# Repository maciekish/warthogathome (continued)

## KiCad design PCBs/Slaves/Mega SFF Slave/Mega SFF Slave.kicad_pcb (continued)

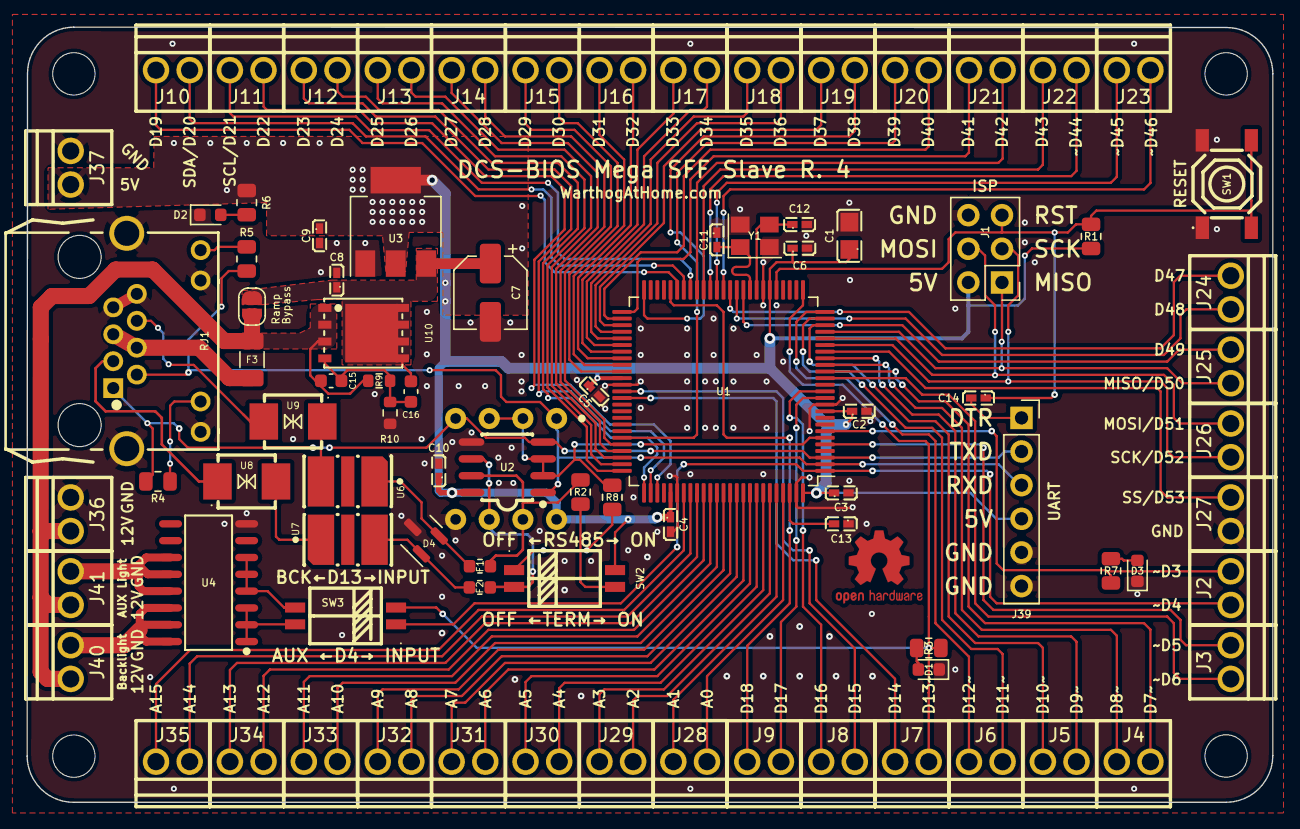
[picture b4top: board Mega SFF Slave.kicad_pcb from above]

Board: 2 copper layers, 94.1 x 58.5 mm, 93 parts (0 on the bottom side), 100 nets.

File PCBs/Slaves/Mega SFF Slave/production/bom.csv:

Designator,Footprint,Quantity,Value,LCSC Part #
U9,DO-214AA_L4.4-W3.6-LS5.3-BI,1,TISP4240M3BJR-S,C840526
J28,CONN-TH_XY308-2.54-2P,1,Screw_Terminal_01x02,C557685
J11,CONN-TH_XY308-2.54-2P,1,Screw_Terminal_01x02,C557685
J2,CONN-TH_XY308-2.54-2P,1,Screw_Terminal_01x02,C557685
J15,CONN-TH_XY308-2.54-2P,1,Screw_Terminal_01x02,C557685
J5,CONN-TH_XY308-2.54-2P,1,Screw_Terminal_01x02,C557685
J36,CONN-TH_XY308-2.54-2P,1,Screw_Terminal_01x02,C557685
J7,CONN-TH_XY308-2.54-2P,1,Screw_Terminal_01x02,C557685
J21,CONN-TH_XY308-2.54-2P,1,Screw_Terminal_01x02,C557685
J17,CONN-TH_XY308-2.54-2P,1,Screw_Terminal_01x02,C557685
J19,CONN-TH_XY308-2.54-2P,1,Screw_Terminal_01x02,C557685
J4,CONN-TH_XY308-2.54-2P,1,Screw_Terminal_01x02,C557685
J9,CONN-TH_XY308-2.54-2P,1,Screw_Terminal_01x02,C557685
J6,CONN-TH_XY308-2.54-2P,1,Screw_Terminal_01x02,C557685
J20,CONN-TH_XY308-2.54-2P,1,Screw_Terminal_01x02,C557685
J10,CONN-TH_XY308-2.54-2P,1,Screw_Terminal_01x02,C557685
J40,CONN-TH_XY308-2.54-2P,1,Screw_Terminal_01x02,C557685
J30,CONN-TH_XY308-2.54-2P,1,Screw_Terminal_01x02,C557685
J37,CONN-TH_XY308-2.54-2P,1,Screw_Terminal_01x02,C557685
J33,CONN-TH_XY308-2.54-2P,1,Screw_Terminal_01x02,C557685
J8,CONN-TH_XY308-2.54-2P,1,Screw_Terminal_01x02,C557685
J25,CONN-TH_XY308-2.54-2P,1,Screw_Terminal_01x02,C557685
J12,CONN-TH_XY308-2.54-2P,1,Screw_Terminal_01x02,C557685
J3,CONN-TH_XY308-2.54-2P,1,Screw_Terminal_01x02,C557685
J14,CONN-TH_XY308-2.54-2P,1,Screw_Terminal_01x02,C557685
J32,CONN-TH_XY308-2.54-2P,1,Screw_Terminal_01x02,C557685
J18,CONN-TH_XY308-2.54-2P,1,Screw_Terminal_01x02,C557685
J23,CONN-TH_XY308-2.54-2P,1,Screw_Terminal_01x02,C557685
J31,CONN-TH_XY308-2.54-2P,1,Screw_Terminal_01x02,C557685
J27,CONN-TH_XY308-2.54-2P,1,Screw_Terminal_01x02,C557685
J13,CONN-TH_XY308-2.54-2P,1,Screw_Terminal_01x02,C557685
J16,CONN-TH_XY308-2.54-2P,1,Screw_Terminal_01x02,C557685
J22,CONN-TH_XY308-2.54-2P,1,Screw_Terminal_01x02,C557685
J24,CONN-TH_XY308-2.54-2P,1,Screw_Terminal_01x02,C557685
J29,CONN-TH_XY308-2.54-2P,1,Screw_Terminal_01x02,C557685
J26,CONN-TH_XY308-2.54-2P,1,Screw_Terminal_01x02,C557685
J41,CONN-TH_XY308-2.54-2P,1,Screw_Terminal_01x02,C557685
J35,CONN-TH_XY308-2.54-2P,1,Screw_Terminal_01x02,C557685
J34,CONN-TH_XY308-2.54-2P,1,Screw_Terminal_01x02,C557685
C4,C0402,1,1uF,C52923
SW1,SW-SMD_4P-L5.1-W5.1-P3.70-LS6.5-TL-2,1,SW_MEC_5E,C318884
U5,DIP-8_W7.62mm,1,MAX487ESA+T,C9953
J1,PinHeader_2x03_P2.54mm_Vertical,1,AVR-ISP-6,C492420
D4,SOT-23,1,SM712_SOT23,C558433
U4,SOP-16_L10.0-W3.9-P1.27-LS6.0-BL,1,ULN2003A,C7512
R1,R_0805_2012Metric,1,10K,C17414
C6,C0402,1,1uF,C52923
C8,C0402,1,10uF,C15525
SW3,SW-SMD_DSHP02TSGER,1,SW_DIP_x02,C367376
RJ1,RJ45-TH_B-1-1,1,RJ45-B-1*1,C138392
J39,PinSocket_1x06_P2.54mm_Vertical,1,Conn_01x06_Female,C40877
U6,DIO-SMD_3P-L6.5-W4.0-BI,1,TBU-CA065-200-WH,C913221
U7,DIO-SMD_3P-L6.5-W4.0-BI,1,TBU-CA065-200-WH,C913221
C9,C0402,1,1uF,C52923
C12,C0402,1,15pF,C1548
F1,Fuse_0603_1608Metric,1,100mA,C207238
C7,CP_Elec_5x5.4,1,47uF,C96178
R7,R_0805_2012Metric,1,1K,C17513
SW2,SW-SMD_DSHP02TSGER,1,SW_DIP_x02,C367376
C13,C0402,1,100nF,C1525
U2,SOIC-8_L5.0-W4.0-P1.27-LS6.0-BL,1,MAX487ESA+T,C9953
R2,R_0805_2012Metric,1,120R,C17437
U3,SOT-223-3_TabPin2,1,AMS1117-5.0,C6187
C2,C0402,1,1uF,C52923
C14,C0402,1,100nF,C1525
U10,DFN-8_L5.9-W5.2-P1.27-LS6.2-BL,1,HY15P03C2,C123687
D2,LED_0603_1608Metric,1,LED,C72041
C16,C_0603_1608Metric,1,47nF,C1622
U1,TQFP-100_14x14mm_P0.5mm,1,ATmega2560-16A,C22460
C1,C0805,1,4.7uF,C1779
R3,R_0805_2012Metric,1,1K,C17513
C5,C0402,1,1uF,C52923
R4,R_0805_2012Metric,1,1.8K,C17398
U8,DO-214AA_L4.4-W3.6-LS5.3-BI,1,TISP4240M3BJR-S,C840526
D1,LED_0603_1608Metric,1,LED,C72041
R9,R_0603_1608Metric,1,10M,C7250
R8,R_0805_2012Metric,1,1K,C17513
C3,C0402,1,1uF,C52923
C10,C0402,1,1uF,C52923
C15,C_0603_1608Metric,1,470nF,C1623
JP1,SolderJumper-2_P1.3mm_Open_RoundedPad1.0x1.5mm,1,Solder,
F3,Fuse_1206_3216Metric,1,500mA,C369159
C11,C0402,1,15pF,C1548
R10,R_0603_1608Metric,1,1M,C22935
Y1,Crystal_SMD_3225-4Pin_3.2x2.5mm,1,Crystal_GND24,C13738
F2,Fuse_0603_1608Metric,1,100mA,C207238
R5,R_0805_2012Metric,1,1.8K,C17398
R6,R_0805_2012Metric,1,1K,C17513
D3,LED_0603_1608Metric,1,LED,C72041

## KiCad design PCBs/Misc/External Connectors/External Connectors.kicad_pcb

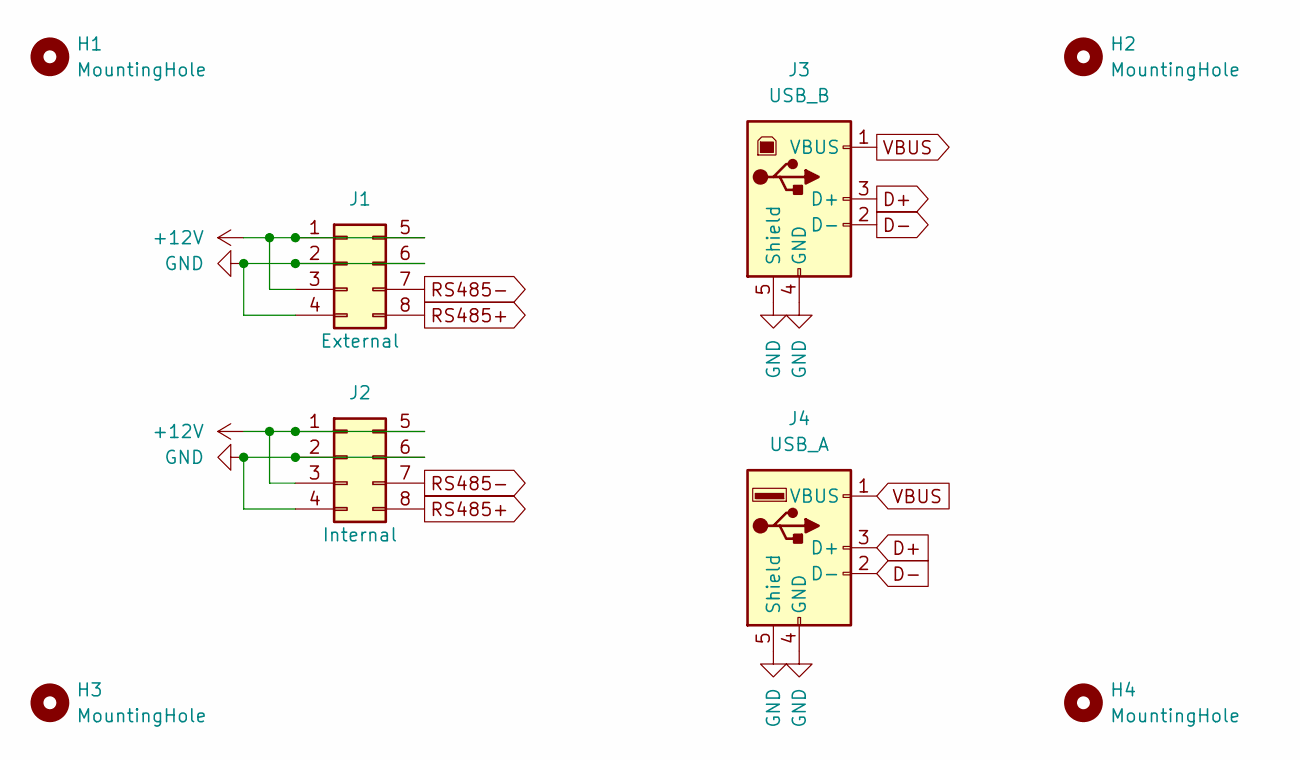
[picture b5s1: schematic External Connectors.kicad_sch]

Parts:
H1, H2, H3, H4: MountingHole; MountingHole_3.2mm_M3
J1, J2: Conn_02x04_Top_Bottom; Molex Micro-Fit 3.0 43045-0800; LCSC C234189
J3: USB_B; USB-B-TH_67068-8000; LCSC C114097
J4: USB_A; USB-A-TH_USB-302-T; LCSC C86461

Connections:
+12V: J1.1, J1.3, J1.5, J2.1, J2.3, J2.5
D+: J3.3 (D+), J4.3 (D+)
D-: J3.2 (D-), J4.2 (D-)
GND: J1.2, J1.4, J1.6, J2.2, J2.4, J2.6, J3.4 (GND), J3.5 (Shield), J4.4 (GND), J4.5 (Shield)
RS485+: J1.8, J2.8
RS485-: J1.7, J2.7
VBUS: J3.1 (VBUS), J4.1 (VBUS)

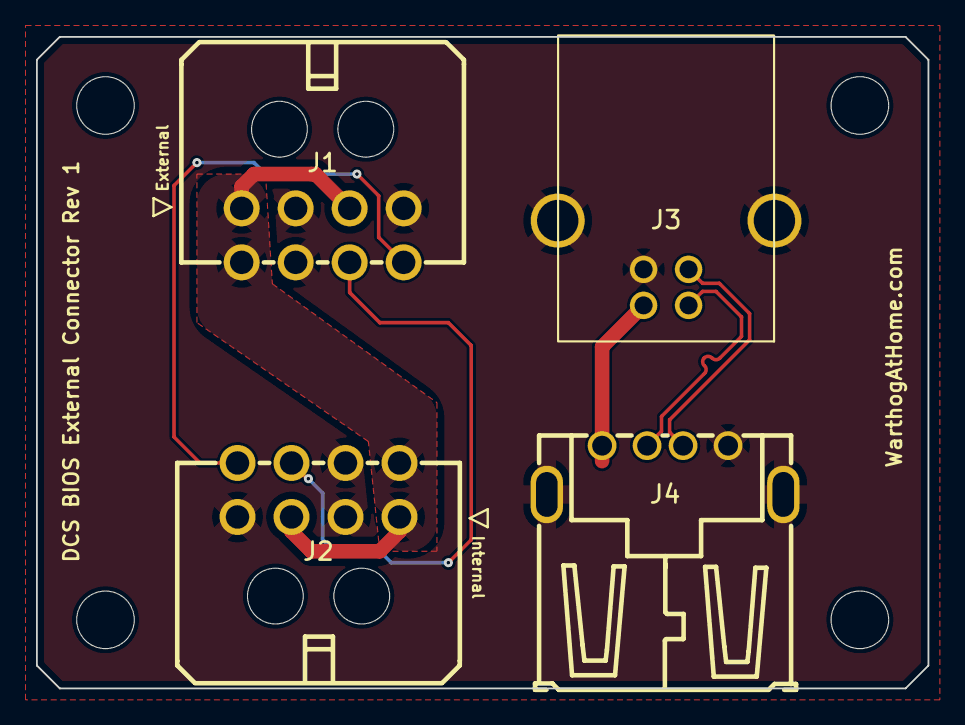
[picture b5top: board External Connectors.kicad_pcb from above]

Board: 2 copper layers, 49.5 x 36.2 mm, 8 parts (0 on the bottom side), 7 nets.

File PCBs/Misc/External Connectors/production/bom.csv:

Designator,Footprint,Quantity,Value,LCSC Part #
J4,USB-A-TH_USB-302-T,1,USB_A,C86461
J3,USB-B-TH_67068-8000,1,USB_B,C114097
J1,Molex Micro-Fit 3.0 43045-0800,1,Conn_02x04_Top_Bottom,C234189
J2,Molex Micro-Fit 3.0 43045-0800,1,Conn_02x04_Top_Bottom,C234189

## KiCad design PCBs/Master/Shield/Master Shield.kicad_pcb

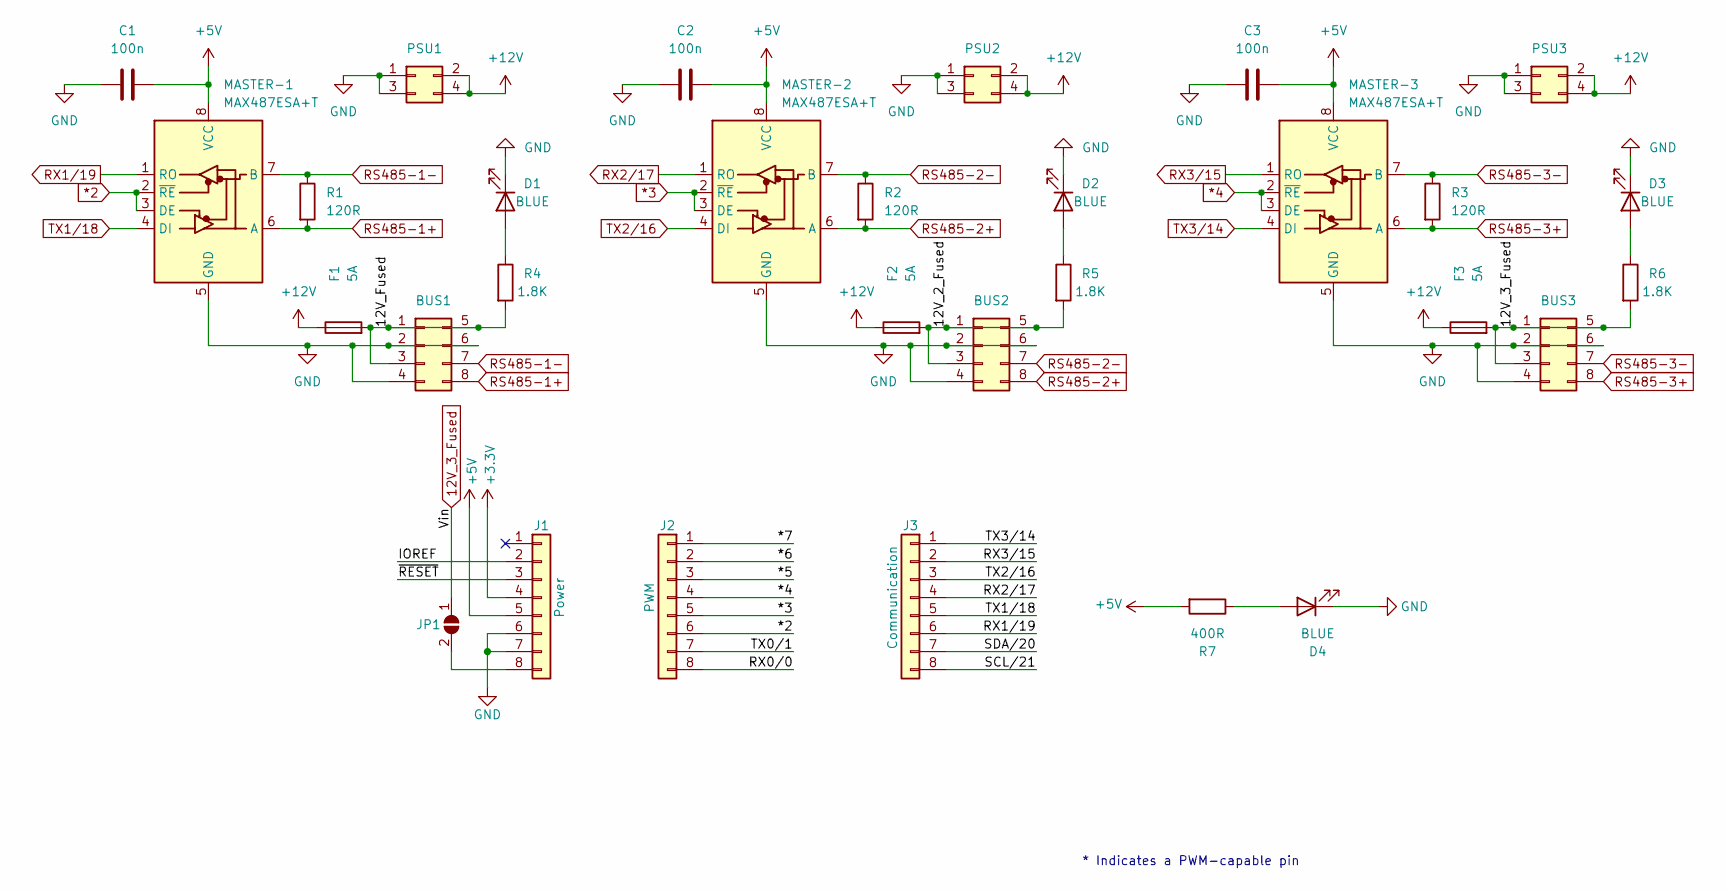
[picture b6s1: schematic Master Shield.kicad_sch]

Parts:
BUS1, BUS2, BUS3: Conn_02x04_Top_Bottom; CONN-TH_430450812; LCSC C277661
C1, C2, C3: 100n; C0402; LCSC C1525
D1, D2, D3, D4: BLUE; LED_0603_1608Metric; LCSC C72041
F1, F2, F3: 5A; FUSE_BK-6013; LCSC C492610
J1: Power; PinHeader_1x08_P2.54mm_Vertical; LCSC C124381
J2: PWM; PinHeader_1x08_P2.54mm_Vertical; LCSC C124381
J3: Communication; PinHeader_1x08_P2.54mm_Vertical; LCSC C124381
JP1: SolderJumper_2_Open; SolderJumper-2_P1.3mm_Open_RoundedPad1.0x1.5mm
MASTER-1, MASTER-2, MASTER-3: MAX487ESA+T; SOIC-8_L5.0-W4.0-P1.27-LS6.0-BL; LCSC C9953
PSU1, PSU2, PSU3: Conn_02x02_Top_Bottom; CONN-TH_0430450400
R1, R2, R3: 120R; R_0805_2012Metric; LCSC C17437
R4, R5, R6: 1.8K; R_0805_2012Metric; LCSC C17398
R7: 400R; R_0805_2012Metric; LCSC C17655

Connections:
12V_3_Fused: BUS3.1, BUS3.3, BUS3.5, F3.2, JP1.1 (A), R6.2
*2: J2.6, MASTER-1.2 (~RE), MASTER-1.3 (DE)
*3: J2.5, MASTER-2.2 (~RE), MASTER-2.3 (DE)
*4: J2.4, MASTER-3.2 (~RE), MASTER-3.3 (DE)
+3V3: J1.4
+5V: C1.2, C2.2, C3.2, J1.5, MASTER-1.8 (VCC), MASTER-2.8 (VCC), MASTER-3.8 (VCC), R7.2
/12V_2_Fused: BUS2.1, BUS2.3, BUS2.5, F2.2, R5.2
/12V_Fused: BUS1.1, BUS1.3, BUS1.5, F1.2, R4.2
/*5: J2.3
/*6: J2.2
/*7: J2.1
/IOREF: J1.2
/RX0/0: J2.8
/SCL/21: J3.8
/SDA/20: J3.7
/TX0/1: J2.7
/~RESET: J1.3
GND: BUS1.2, BUS1.4, BUS1.6, BUS2.2, BUS2.4, BUS2.6, BUS3.2, BUS3.4, BUS3.6, C1.1, C2.1, C3.1, D1.1 (K), D2.1 (K), D3.1 (K), D4.1 (K), J1.6, J1.7, MASTER-1.5 (GND), MASTER-2.5 (GND), MASTER-3.5 (GND), PSU1.1, PSU1.3, PSU2.1, PSU2.3, PSU3.1, PSU3.3
unnamed: D1.2 (A), R4.1
unnamed: D2.2 (A), R5.1
unnamed: D3.2 (A), R6.1
unnamed: D4.2 (A), R7.1
unnamed: J1.8, JP1.2 (B)
RS485-1+: BUS1.8, MASTER-1.6 (A), R1.2
RS485-1-: BUS1.7, MASTER-1.7 (B), R1.1
RS485-2+: BUS2.8, MASTER-2.6 (A), R2.2
RS485-2-: BUS2.7, MASTER-2.7 (B), R2.1
RS485-3+: BUS3.8, MASTER-3.6 (A), R3.2
RS485-3-: BUS3.7, MASTER-3.7 (B), R3.1
RX1/19: J3.6, MASTER-1.1 (RO)
RX2/17: J3.4, MASTER-2.1 (RO)
RX3/15: J3.2, MASTER-3.1 (RO)
TX1/18: J3.5, MASTER-1.4 (DI)
TX2/16: J3.3, MASTER-2.4 (DI)
TX3/14: J3.1, MASTER-3.4 (DI)

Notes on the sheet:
* Indicates a PWM-capable pin

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
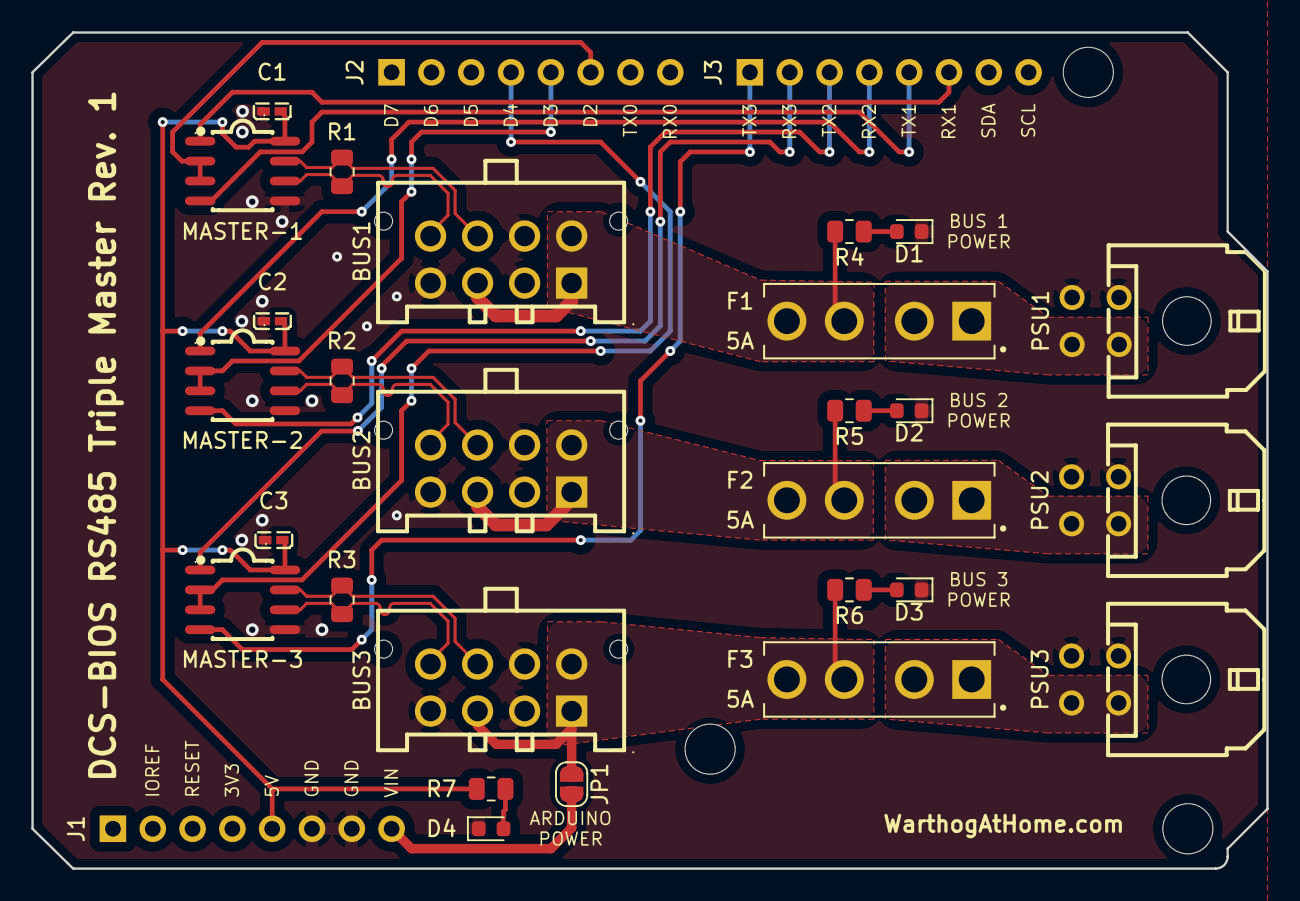
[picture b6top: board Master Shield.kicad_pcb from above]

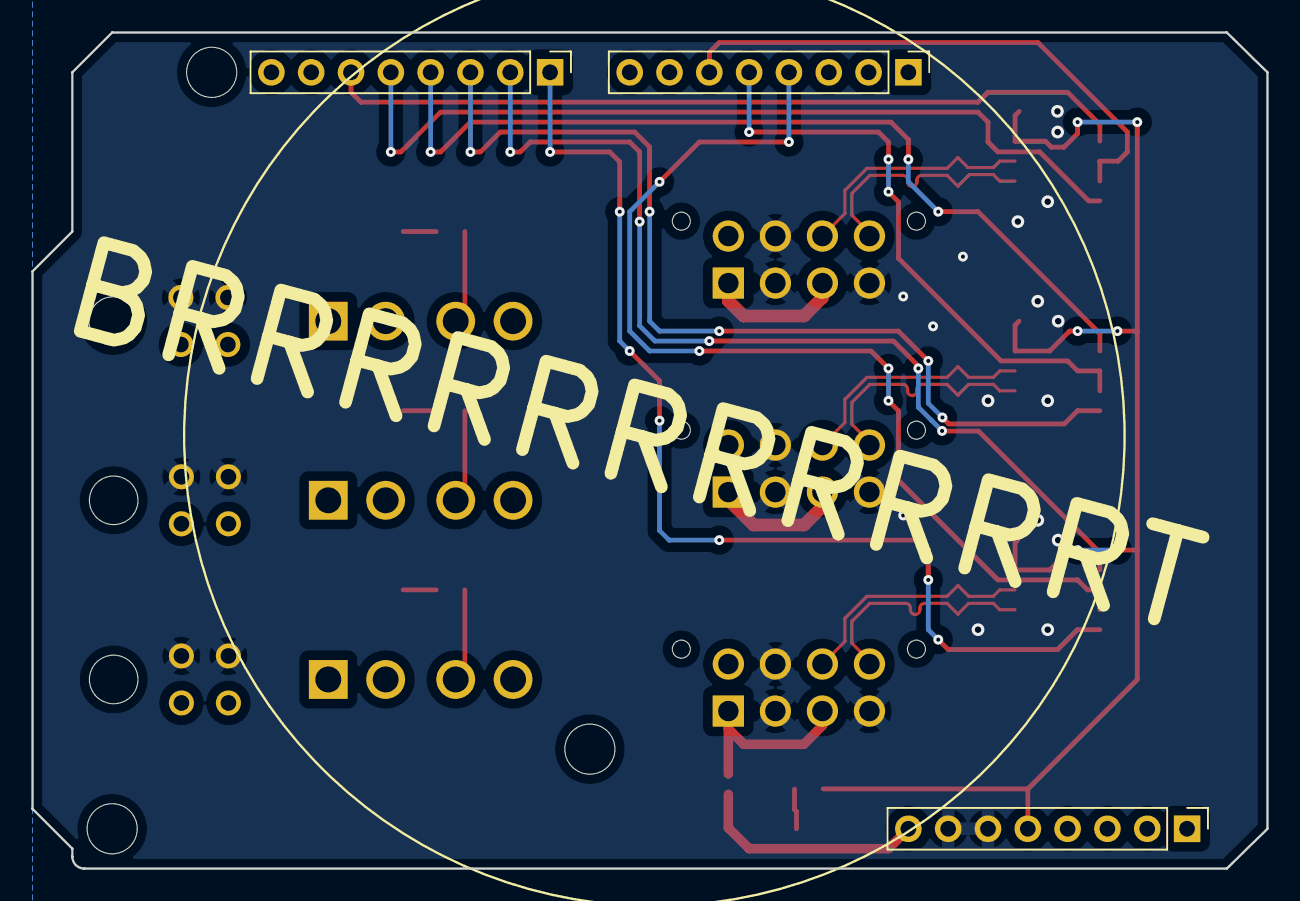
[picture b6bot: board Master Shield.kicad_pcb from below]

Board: 2 copper layers, 78.8 x 53.3 mm, 33 parts (3 on the bottom side), 28 nets.

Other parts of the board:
MH4, MH5, MH6: MountingHole_3.2mm

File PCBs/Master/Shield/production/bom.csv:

Designator,Footprint,Quantity,Value,LCSC Part #
R2,R_0805_2012Metric,1,120R,C17437
MASTER-2,SOIC-8_L5.0-W4.0-P1.27-LS6.0-BL,1,MAX487ESA+T,C9953
R4,R_0805_2012Metric,1,1.8K,C17398
D3,LED_0603_1608Metric,1,BLUE,C72041
BUS3,CONN-TH_430450812,1,Conn_02x04_Top_Bottom,C277661
C1,C0402,1,100n,C1525
C3,C0402,1,100n,C1525
R5,R_0805_2012Metric,1,1.8K,C17398
MASTER-1,SOIC-8_L5.0-W4.0-P1.27-LS6.0-BL,1,MAX487ESA+T,C9953
D1,LED_0603_1608Metric,1,BLUE,C72041
D2,LED_0603_1608Metric,1,BLUE,C72041
JP1,SolderJumper-2_P1.3mm_Open_RoundedPad1.0x1.5mm,1,SolderJumper_2_Open,
D4,LED_0603_1608Metric,1,BLUE,C72041
C2,C0402,1,100n,C1525
R6,R_0805_2012Metric,1,1.8K,C17398
R7,R_0805_2012Metric,1,400R,C17655
BUS2,CONN-TH_430450812,1,Conn_02x04_Top_Bottom,C277661
MASTER-3,SOIC-8_L5.0-W4.0-P1.27-LS6.0-BL,1,MAX487ESA+T,C9953
R1,R_0805_2012Metric,1,120R,C17437
R3,R_0805_2012Metric,1,120R,C17437
BUS1,CONN-TH_430450812,1,Conn_02x04_Top_Bottom,C277661
J1,PinHeader_1x08_P2.54mm_Vertical,1,Power,C124381
J2,PinHeader_1x08_P2.54mm_Vertical,1,PWM,C124381
J3,PinHeader_1x08_P2.54mm_Vertical,1,Communication,C124381

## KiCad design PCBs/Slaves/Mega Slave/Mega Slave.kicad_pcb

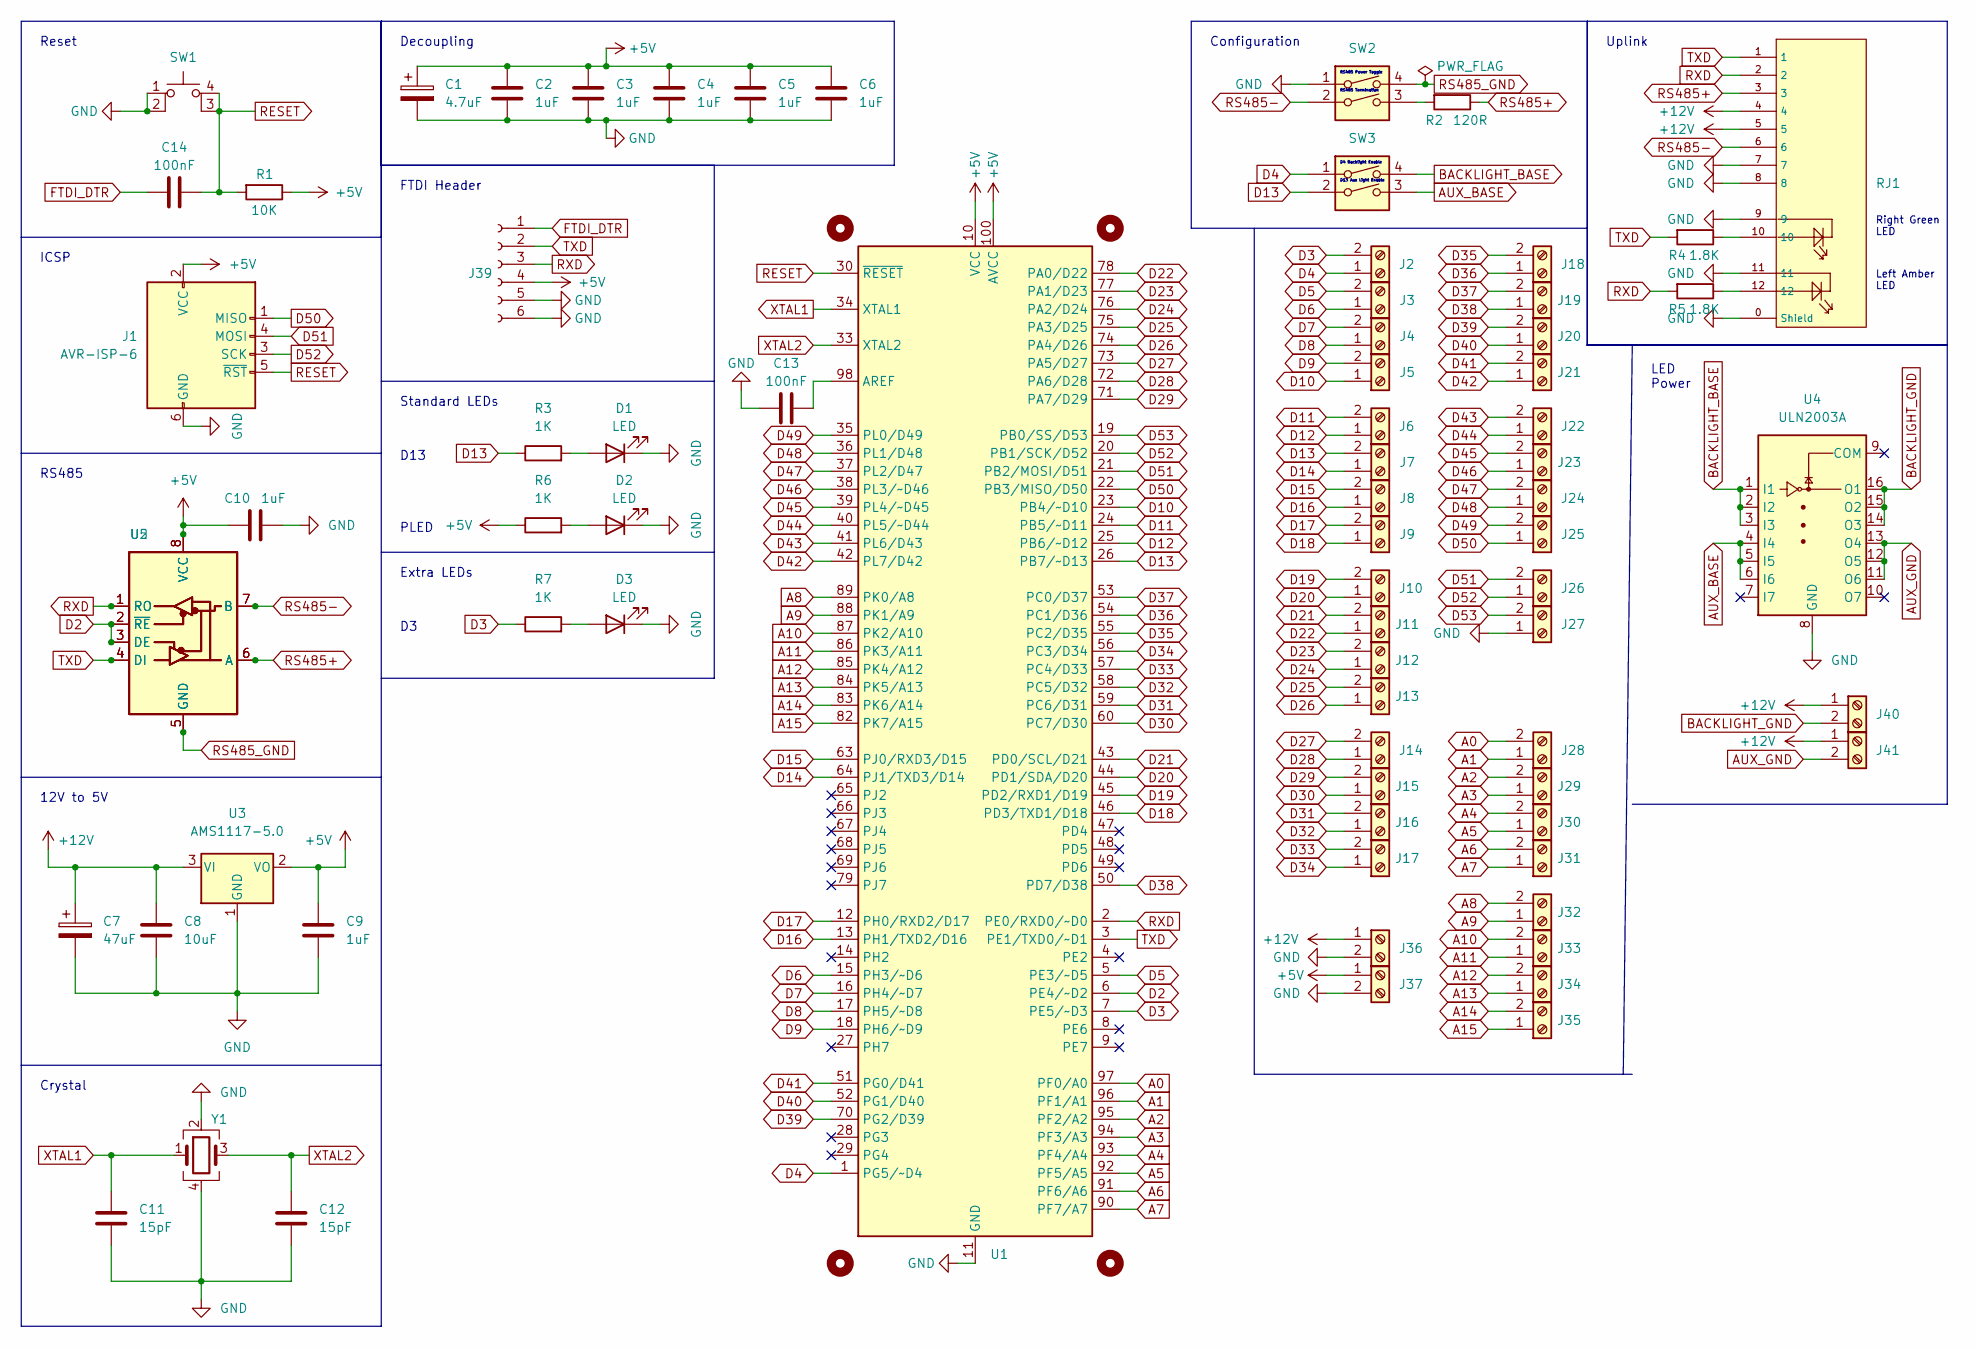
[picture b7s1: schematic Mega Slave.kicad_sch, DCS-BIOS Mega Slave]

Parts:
C1: 4.7uF; C0805; LCSC C1779
C2, C3, C4, C5, C6, C9, C10: 1uF; C0402; LCSC C52923
C7: 47uF; CP_Elec_5x5.4; LCSC C96178
C8: 10uF; C0402; LCSC C15525
C11, C12: 15pF; C0402; LCSC C1548
C13, C14: 100nF; C0402; LCSC C1525
D1, D2, D3: LED; LED_0603_1608Metric; LCSC C72041
H1, H2, H3, H4: MountingHole; MountingHole_3.2mm_M3
J1: AVR-ISP-6; PinHeader_2x03_P2.54mm_Vertical; LCSC C492420
J2, J3, J4, J5, J6, J7, J8, J9, J10, J11, J12, J13, J14, J15, J16, J17, J18, J19, J20, J21, J22, J23, J24, J25, J26, J27, J28, J29, J30, J31, J32, J33, J34, J35, J36, J37, J40, J41: Screw_Terminal_01x02; CONN-TH_WJ126V-5.0-2P; LCSC C8404
J39: Conn_01x06_Female; PinSocket_1x06_P2.54mm_Vertical; LCSC C40877
R1: 10K; R_0805_2012Metric; LCSC C17414
R2: 120R; R_0805_2012Metric; LCSC C17437
R3, R6, R7: 1K; R_0805_2012Metric; LCSC C17513
R4, R5: 1.8K; R_0805_2012Metric; LCSC C17398
RJ1: RJ45-B-1*1; RJ45-TH_B-1-1; LCSC C138392
SW1: SW_MEC_5E; SW-SMD_4P-L5.1-W5.1-P3.70-LS6.5-TL-2; LCSC C318884
SW2, SW3: SW_DIP_x02; SW-SMD_DSHP02TSGER; LCSC C367376
U1: ATmega2560-16A; TQFP-100_14x14mm_P0.5mm; LCSC C22460
U2: MAX487ESA+T; SOIC-8_L5.0-W4.0-P1.27-LS6.0-BL; LCSC C9953
U3: AMS1117-5.0; SOT-223-3_TabPin2; LCSC C6187
U4: ULN2003A; SOP-16_L10.0-W3.9-P1.27-LS6.0-BL; LCSC C7512
U5: MAX487ESA+T; DIP-8_W7.62mm; LCSC C9953
Y1: Crystal_GND24; Crystal_SMD_3225-4Pin_3.2x2.5mm; LCSC C13738

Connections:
+5V: C1.1, C2.1, C3.1, C4.1, C5.1, C6.1, C9.1, C10.1, J1.2 (VCC), J37.1, J39.4, R1.1, R6.1, U1.10 (VCC), U1.31 (VCC), U1.61 (VCC), U1.80 (VCC), U1.100 (AVCC), U2.8 (VCC), U3.2 (VO), U5.8 (VCC)
+12V: C7.1, C8.1, J36.1, J40.1, J41.1, RJ1.4, RJ1.5, U3.3 (VI)
A0: J28.2, U1.97 (PF0/A0)
A1: J28.1, U1.96 (PF1/A1)
A2: J29.2, U1.95 (PF2/A2)
A3: J29.1, U1.94 (PF3/A3)
A4: J30.2, U1.93 (PF4/A4)
A5: J30.1, U1.92 (PF5/A5)
A6: J31.2, U1.91 (PF6/A6)
A7: J31.1, U1.90 (PF7/A7)
A8: J32.2, U1.89 (PK0/A8)
A9: J32.1, U1.88 (PK1/A9)
A10: J33.2, U1.87 (PK2/A10)
A11: J33.1, U1.86 (PK3/A11)
A12: J34.2, U1.85 (PK4/A12)
A13: J34.1, U1.84 (PK5/A13)
A14: J35.2, U1.83 (PK6/A14)
A15: J35.1, U1.82 (PK7/A15)
AUX_BASE: SW3.3, U4.4 (I4), U4.5 (I5), U4.6 (I6)
AUX_GND: J41.2, U4.11 (O6), U4.12 (O5), U4.13 (O4)
BACKLIGHT_BASE: SW3.4, U4.1 (I1), U4.2 (I2), U4.3 (I3)
BACKLIGHT_GND: J40.2, U4.14 (O3), U4.15 (O2), U4.16 (O1)
D2: U1.6 (PE4/~D2), U2.2 (~RE), U2.3 (DE), U5.2 (~RE), U5.3 (DE)
D3: J2.2, R7.1, U1.7 (PE5/~D3)
D4: J2.1, SW3.1, U1.1 (PG5/~D4)
D5: J3.2, U1.5 (PE3/~D5)
D6: J3.1, U1.15 (PH3/~D6)
D7: J4.2, U1.16 (PH4/~D7)
D8: J4.1, U1.17 (PH5/~D8)
D9: J5.2, U1.18 (PH6/~D9)
D10: J5.1, U1.23 (PB4/~D10)
D11: J6.2, U1.24 (PB5/~D11)
D12: J6.1, U1.25 (PB6/~D12)
D13: J7.2, R3.1, SW3.2, U1.26 (PB7/~D13)
D14: J7.1, U1.64 (PJ1/TXD3/D14)
D15: J8.2, U1.63 (PJ0/RXD3/D15)
D16: J8.1, U1.13 (PH1/TXD2/D16)
D17: J9.2, U1.12 (PH0/RXD2/D17)
D18: J9.1, U1.46 (PD3/TXD1/D18)
D19: J10.2, U1.45 (PD2/RXD1/D19)
D20: J10.1, U1.44 (PD1/SDA/D20)
D21: J11.2, U1.43 (PD0/SCL/D21)
D22: J11.1, U1.78 (PA0/D22)
D23: J12.2, U1.77 (PA1/D23)
D24: J12.1, U1.76 (PA2/D24)
D25: J13.2, U1.75 (PA3/D25)
D26: J13.1, U1.74 (PA4/D26)
D27: J14.2, U1.73 (PA5/D27)
D28: J14.1, U1.72 (PA6/D28)
D29: J15.2, U1.71 (PA7/D29)
D30: J15.1, U1.60 (PC7/D30)
D31: J16.2, U1.59 (PC6/D31)
D32: J16.1, U1.58 (PC5/D32)
D33: J17.2, U1.57 (PC4/D33)
D34: J17.1, U1.56 (PC3/D34)
D35: J18.2, U1.55 (PC2/D35)
D36: J18.1, U1.54 (PC1/D36)
D37: J19.2, U1.53 (PC0/D37)
D38: J19.1, U1.50 (PD7/D38)
D39: J20.2, U1.70 (PG2/D39)
D40: J20.1, U1.52 (PG1/D40)
D41: J21.2, U1.51 (PG0/D41)
D42: J21.1, U1.42 (PL7/D42)
D43: J22.2, U1.41 (PL6/D43)
D44: J22.1, U1.40 (PL5/~D44)
D45: J23.2, U1.39 (PL4/~D45)
D46: J23.1, U1.38 (PL3/~D46)
D47: J24.2, U1.37 (PL2/D47)
D48: J24.1, U1.36 (PL1/D48)
D49: J25.2, U1.35 (PL0/D49)
D50: J1.1 (MISO), J25.1, U1.22 (PB3/MISO/D50)
D51: J1.4 (MOSI), J26.2, U1.21 (PB2/MOSI/D51)
D52: J1.3 (SCK), J26.1, U1.20 (PB1/SCK/D52)
D53: J27.2, U1.19 (PB0/SS/D53)
FTDI_DTR: C14.2, J39.1
GND: C1.2, C2.2, C3.2, C4.2, C5.2, C6.2, C7.2, C8.2, C9.2, C10.2, C11.1, C12.2, C13.1, D1.1 (K), D2.1 (K), D3.1 (K), J1.6 (GND), J27.1, J36.2, J37.2, J39.5, J39.6, RJ1.0 (Shield), RJ1.7, RJ1.8, RJ1.9, RJ1.11, SW1.1, SW1.2, SW2.1, U1.11 (GND), U1.32 (GND), U1.62 (GND), U1.81 (GND), U1.99 (GND), U3.1 (GND), U4.8 (GND), Y1.2, Y1.4
unnamed: C13.2, U1.98 (AREF)
unnamed: D1.2 (A), R3.2
unnamed: D2.2 (A), R6.2
unnamed: D3.2 (A), R7.2
unnamed: R2.2, SW2.3
unnamed: R4.1, RJ1.10
unnamed: R5.1, RJ1.12
RESET: C14.1, J1.5 (~RST), R1.2, SW1.3 (K), SW1.4 (A), U1.30 (~RESET)
RS485+: R2.1, RJ1.3, U2.6 (A), U5.6 (A)
RS485-: RJ1.6, SW2.2, U2.7 (B), U5.7 (B)
RS485_GND: SW2.4, U2.5 (GND), U5.5 (GND)
RXD: J39.3, R5.2, RJ1.2, U1.2 (PE0/RXD0/~D0), U2.1 (RO), U5.1 (RO)
TXD: J39.2, R4.2, RJ1.1, U1.3 (PE1/TXD0/~D1), U2.4 (DI), U5.4 (DI)
XTAL1: C11.2, U1.34 (XTAL1), Y1.1
XTAL2: C12.1, U1.33 (XTAL2), Y1.3

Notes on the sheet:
RS485
Reset
LED Power
Right Green LED
Configuration
Crystal
Standard LEDs
Decoupling
Left Amber LED
RS485 Termination
Extra LEDs
D4 Backlight Enable
12V to 5V
RS485 Power Toggle
Uplink
D13 Aux Light Enable
D13
FTDI Header
ICSP
PLED

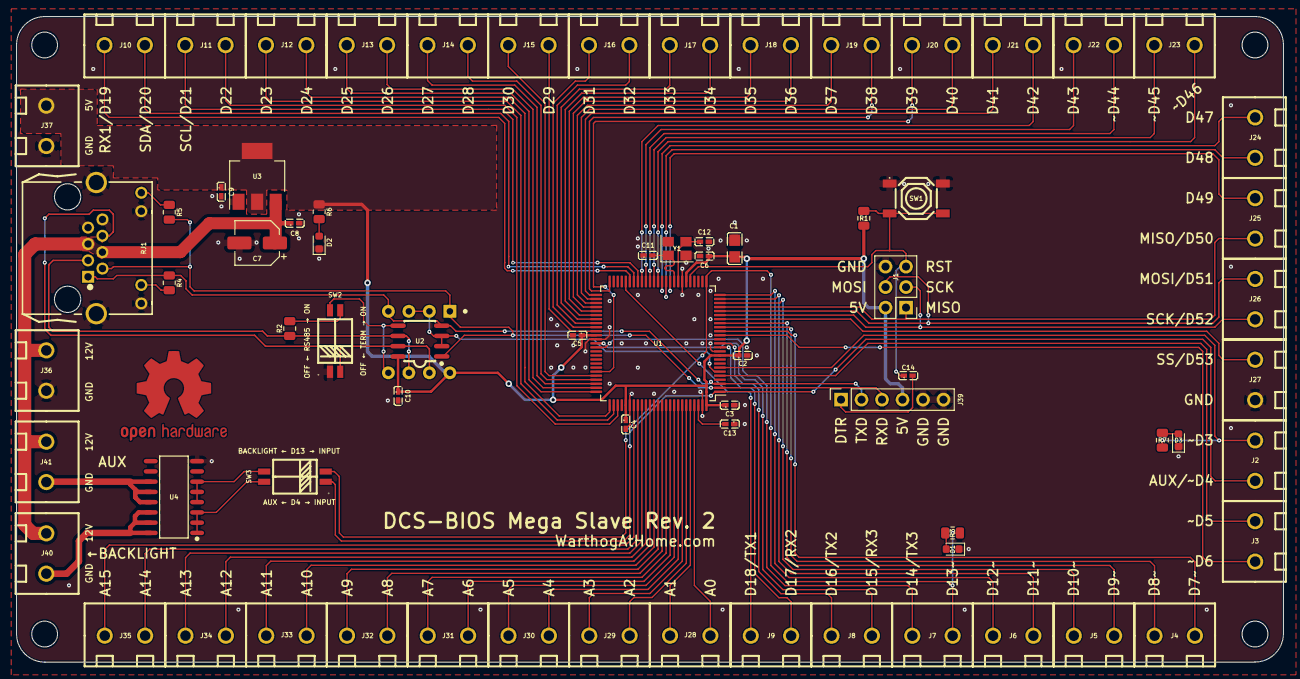
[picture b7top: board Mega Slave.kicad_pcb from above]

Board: 2 copper layers, 157.0 x 80.0 mm, 78 parts (0 on the bottom side), 91 nets.

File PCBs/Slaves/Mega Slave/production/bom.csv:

Designator,Footprint,Quantity,Value,LCSC Part #
J28,CONN-TH_WJ126V-5.0-2P,1,Screw_Terminal_01x02,C557685
J11,CONN-TH_WJ126V-5.0-2P,1,Screw_Terminal_01x02,C557685
C4,C0402,1,1uF,C52923
J2,CONN-TH_WJ126V-5.0-2P,1,Screw_Terminal_01x02,C557685
J15,CONN-TH_WJ126V-5.0-2P,1,Screw_Terminal_01x02,C557685
SW1,SW-SMD_4P-L5.1-W5.1-P3.70-LS6.5-TL-2,1,SW_MEC_5E,C318884
U5,DIP-8_W7.62mm,1,MAX487ESA+T,C9953
J1,PinHeader_2x03_P2.54mm_Vertical,1,AVR-ISP-6,C492420
J5,CONN-TH_WJ126V-5.0-2P,1,Screw_Terminal_01x02,C557685
J36,CONN-TH_WJ126V-5.0-2P,1,Screw_Terminal_01x02,C557685
U4,SOP-16_L10.0-W3.9-P1.27-LS6.0-BL,1,ULN2003A,C7512
J7,CONN-TH_WJ126V-5.0-2P,1,Screw_Terminal_01x02,C557685
J21,CONN-TH_WJ126V-5.0-2P,1,Screw_Terminal_01x02,C557685
J17,CONN-TH_WJ126V-5.0-2P,1,Screw_Terminal_01x02,C557685
J19,CONN-TH_WJ126V-5.0-2P,1,Screw_Terminal_01x02,C557685
R1,R_0805_2012Metric,1,10K,C17414
C6,C0402,1,1uF,C52923
J4,CONN-TH_WJ126V-5.0-2P,1,Screw_Terminal_01x02,C557685
C8,C0402,1,10uF,C15525
SW3,SW-SMD_DSHP02TSGER,1,SW_DIP_x02,C367376
RJ1,RJ45-TH_B-1-1,1,RJ45-B-1*1,C138392
J39,PinSocket_1x06_P2.54mm_Vertical,1,Conn_01x06_Female,C40877
C9,C0402,1,1uF,C52923
C12,C0402,1,15pF,C1548
J9,CONN-TH_WJ126V-5.0-2P,1,Screw_Terminal_01x02,C557685
J6,CONN-TH_WJ126V-5.0-2P,1,Screw_Terminal_01x02,C557685
J20,CONN-TH_WJ126V-5.0-2P,1,Screw_Terminal_01x02,C557685
J10,CONN-TH_WJ126V-5.0-2P,1,Screw_Terminal_01x02,C557685
J40,CONN-TH_WJ126V-5.0-2P,1,Screw_Terminal_01x02,C557685
C7,CP_Elec_5x5.4,1,47uF,C96178
J30,CONN-TH_WJ126V-5.0-2P,1,Screw_Terminal_01x02,C557685
R7,R_0805_2012Metric,1,1K,C17513
J37,CONN-TH_WJ126V-5.0-2P,1,Screw_Terminal_01x02,C557685
SW2,SW-SMD_DSHP02TSGER,1,SW_DIP_x02,C367376
C13,C0402,1,100nF,C1525
J33,CONN-TH_WJ126V-5.0-2P,1,Screw_Terminal_01x02,C557685
J8,CONN-TH_WJ126V-5.0-2P,1,Screw_Terminal_01x02,C557685
U2,SOIC-8_L5.0-W4.0-P1.27-LS6.0-BL,1,MAX487ESA+T,C9953
J25,CONN-TH_WJ126V-5.0-2P,1,Screw_Terminal_01x02,C557685
R2,R_0805_2012Metric,1,120R,C17437
U3,SOT-223-3_TabPin2,1,AMS1117-5.0,C6187
J12,CONN-TH_WJ126V-5.0-2P,1,Screw_Terminal_01x02,C557685
C2,C0402,1,1uF,C52923
C14,C0402,1,100nF,C1525
D2,LED_0603_1608Metric,1,LED,C72041
J3,CONN-TH_WJ126V-5.0-2P,1,Screw_Terminal_01x02,C557685
U1,TQFP-100_14x14mm_P0.5mm,1,ATmega2560-16A,C22460
J14,CONN-TH_WJ126V-5.0-2P,1,Screw_Terminal_01x02,C557685
C1,C0805,1,4.7uF,C1779
R3,R_0805_2012Metric,1,1K,C17513
C5,C0402,1,1uF,C52923
J32,CONN-TH_WJ126V-5.0-2P,1,Screw_Terminal_01x02,C557685
J18,CONN-TH_WJ126V-5.0-2P,1,Screw_Terminal_01x02,C557685
R4,R_0805_2012Metric,1,1.8K,C17398
J23,CONN-TH_WJ126V-5.0-2P,1,Screw_Terminal_01x02,C557685
D1,LED_0603_1608Metric,1,LED,C72041
J31,CONN-TH_WJ126V-5.0-2P,1,Screw_Terminal_01x02,C557685
J27,CONN-TH_WJ126V-5.0-2P,1,Screw_Terminal_01x02,C557685
J13,CONN-TH_WJ126V-5.0-2P,1,Screw_Terminal_01x02,C557685
J16,CONN-TH_WJ126V-5.0-2P,1,Screw_Terminal_01x02,C557685
C3,C0402,1,1uF,C52923
J22,CONN-TH_WJ126V-5.0-2P,1,Screw_Terminal_01x02,C557685
C10,C0402,1,1uF,C52923
J24,CONN-TH_WJ126V-5.0-2P,1,Screw_Terminal_01x02,C557685
J29,CONN-TH_WJ126V-5.0-2P,1,Screw_Terminal_01x02,C557685
J26,CONN-TH_WJ126V-5.0-2P,1,Screw_Terminal_01x02,C557685
C11,C0402,1,15pF,C1548
Y1,Crystal_SMD_3225-4Pin_3.2x2.5mm,1,Crystal_GND24,C13738
J41,CONN-TH_WJ126V-5.0-2P,1,Screw_Terminal_01x02,C557685
J35,CONN-TH_WJ126V-5.0-2P,1,Screw_Terminal_01x02,C557685
J34,CONN-TH_WJ126V-5.0-2P,1,Screw_Terminal_01x02,C557685
R5,R_0805_2012Metric,1,1.8K,C17398
R6,R_0805_2012Metric,1,1K,C17513
D3,LED_0603_1608Metric,1,LED,C72041
